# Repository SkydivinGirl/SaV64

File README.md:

# SaV64
Commodore VIC-20, Commodore 64, and Commodore Plus/4 Over-Voltage Protection

Jointly designed by Heather Kent and Fredric Blåholtz

Electrical Design and PCB Layout: Fredric Blåholtz

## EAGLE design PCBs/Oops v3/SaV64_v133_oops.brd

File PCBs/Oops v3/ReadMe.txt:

Optocoupler Daughter Board for SaV64 v1.33 PCB

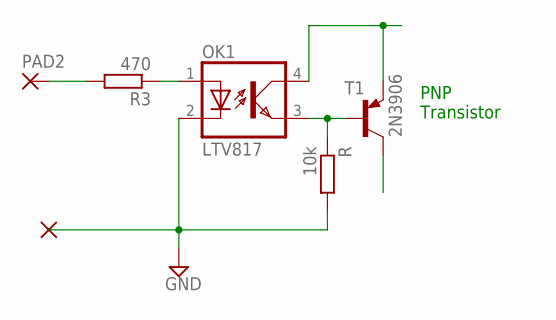
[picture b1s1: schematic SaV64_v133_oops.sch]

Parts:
OK1: LTV817; SMD4
PAD2: 1,6/0,8
R: 10k; R1210W
R3: 470; R1210W
T1: 2N3906; TO92

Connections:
GND: OK1.2 (C), R.2
unnamed: OK1.1 (A), R3.1
unnamed: OK1.3 (EMIT), R.1, T1.2 (B)
unnamed: PAD2.1, R3.2
unnamed: OK1.4 (COL), T1.3 (E)

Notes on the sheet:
PNP Transistor

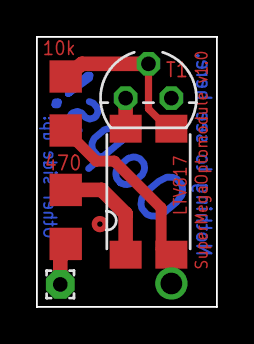
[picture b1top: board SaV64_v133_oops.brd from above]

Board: 2 copper layers, 10.0 x 15.0 mm, 5 parts (0 on the bottom side), 5 nets.

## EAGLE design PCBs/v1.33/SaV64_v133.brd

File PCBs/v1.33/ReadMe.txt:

SaV64 v1.33 PCB
Requires Oops v3 Optocoupler Daughter Board

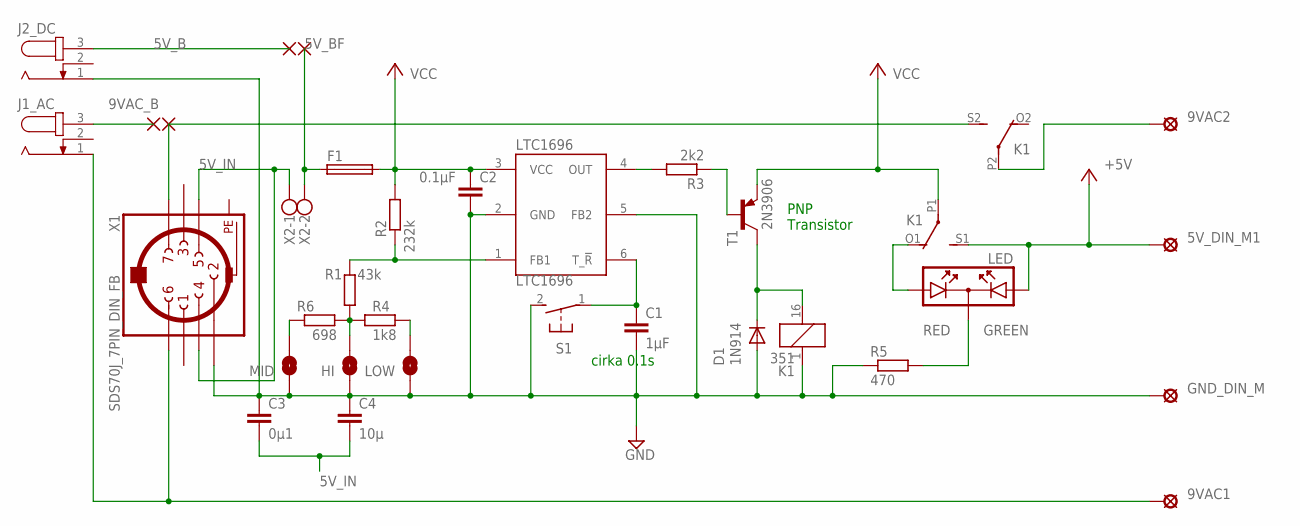
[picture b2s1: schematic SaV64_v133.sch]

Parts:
5V_DIN_M1, 9VAC1, 9VAC2: SE14
C1: 1µF; C050-024X044
C2: 0.1µF; C050-024X044
C3: 0µ1; C050-024X044
C4: 10µ; C050-024X044
D1: 1N914; DO35-10
F1: SHK20L
GND_DIN_M: SE14
HI: SJR; SJ_ROUNDED
J1_AC, J2_DC: JACK-PLUG0; SPC4077
K1: 351
LED: DUOLED
LOW: SJR; SJ_ROUNDED
LTC1696: LTC1696; SOT23-6
MID: SJR; SJ_ROUNDED
R1: 43k; R1206W
R2: 232k; R1206W
R3: 2k2; 0207/10
R4: 1k8; R1206W
R5: 470; 0207/12
R6: 698; R1206W
S1: 31-XX; B3F-31XX
T1: 2N3906; TO92
X1: SDS70J_7PIN_DIN_FB; SDS-70J_7PIN_FEMALE_DIN
X2: W237-102

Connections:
5V_B: J2_DC.3
5V_BF: F1.1A (1), F1.1B (1), X2.2
5V_IN: C3.2, C4.2, X1.4, X1.5, X2.1
9VAC2: 9VAC2.MP, K1.P2
9VAC_B: J1_AC.3
+5V: 5V_DIN_M1.MP, K1.S1 (S), LED.A1
GND: C1.2, C2.2, C3.1, C4.1, D1.A, GND_DIN_M.MP, HI.P$1 (1), J2_DC.1, K1.1, LOW.P$1 (1), LTC1696.2 (GND), LTC1696.5 (FB2), MID.P$1 (1), R5.1, S1.2 (S), X1.2
unnamed: LTC1696.1 (FB1), R1.2, R2.1
unnamed: LED.K, R5.2
unnamed: MID.P$2 (2), R6.1
unnamed: R3.1, T1.2 (B)
unnamed: HI.P$2 (2), R1.1, R4.2, R6.2
unnamed: C1.1, LTC1696.6 (T_!R), S1.1
unnamed: LTC1696.4 (OUT), R3.2
unnamed: K1.S2 (S), X1.7
unnamed: LOW.P$2 (2), R4.1
unnamed: K1.O1 (O), LED.A2
unnamed: D1.C, K1.16 (2), T1.1 (C)
unnamed: 9VAC1.MP, J1_AC.1, X1.6
PE: X1.PE, X1.PE@ (PE)
VCC: C2.1, F1.2A (2), F1.2B (2), K1.P1, LTC1696.3 (VCC), R2.2, T1.3 (E)

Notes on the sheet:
RED
GREEN
cirka 0.1s
PNP Transistor

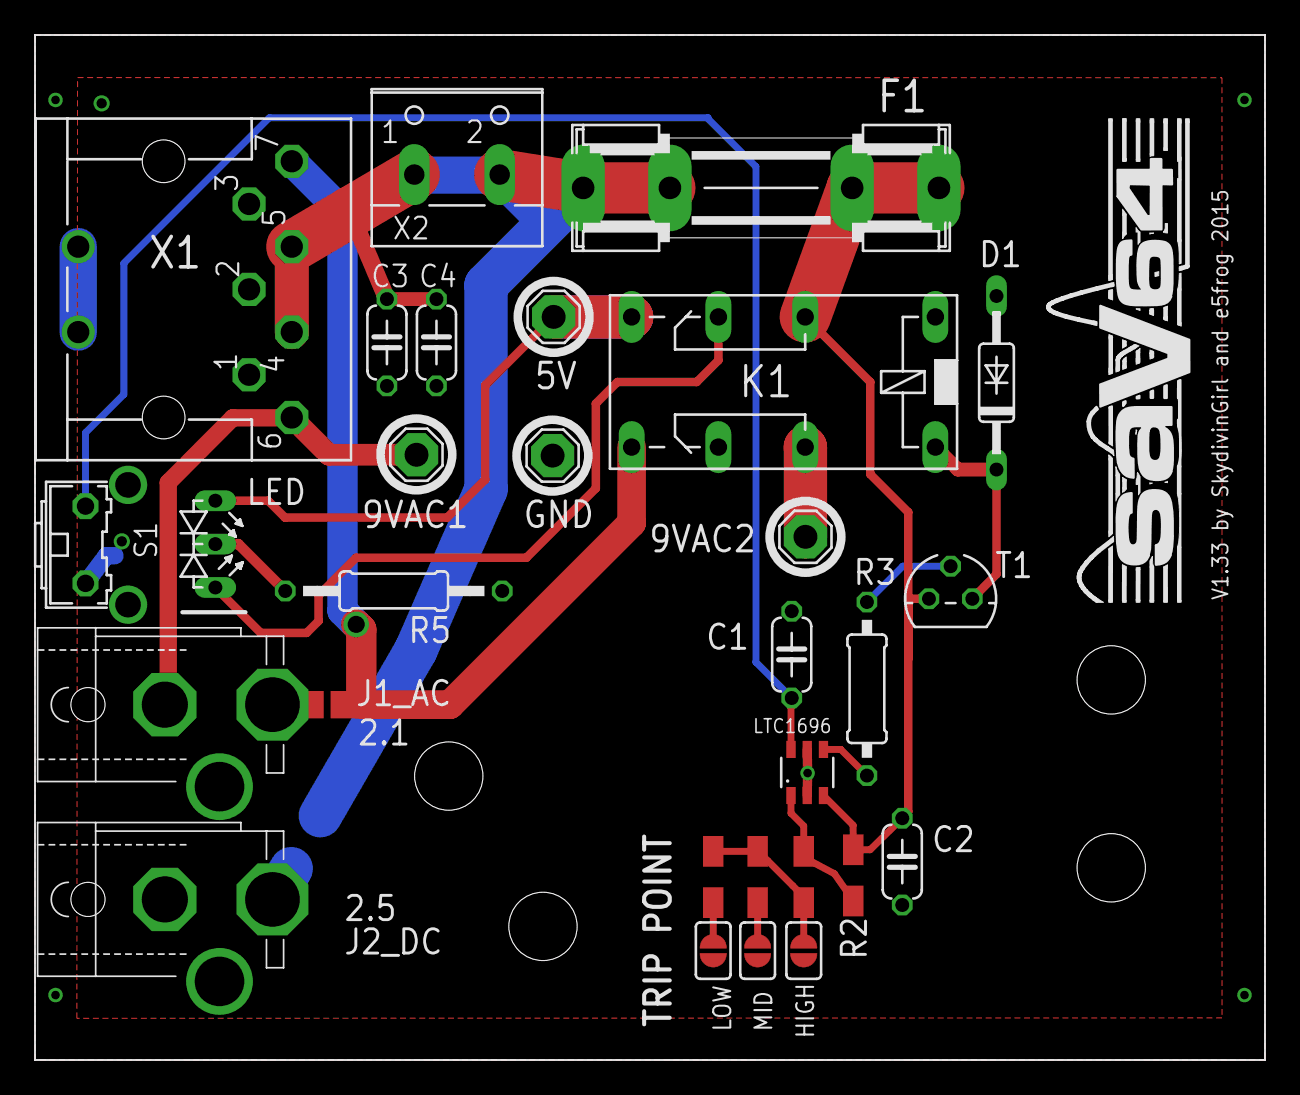
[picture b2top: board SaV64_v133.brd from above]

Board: 2 copper layers, 72.0 x 60.0 mm, 28 parts (0 on the bottom side), 19 nets.

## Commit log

2022-02-07 Added PDF Version of Assembly Instructions
    This PDF Version was created by Clay McCauley from the Word doc in the repository.
